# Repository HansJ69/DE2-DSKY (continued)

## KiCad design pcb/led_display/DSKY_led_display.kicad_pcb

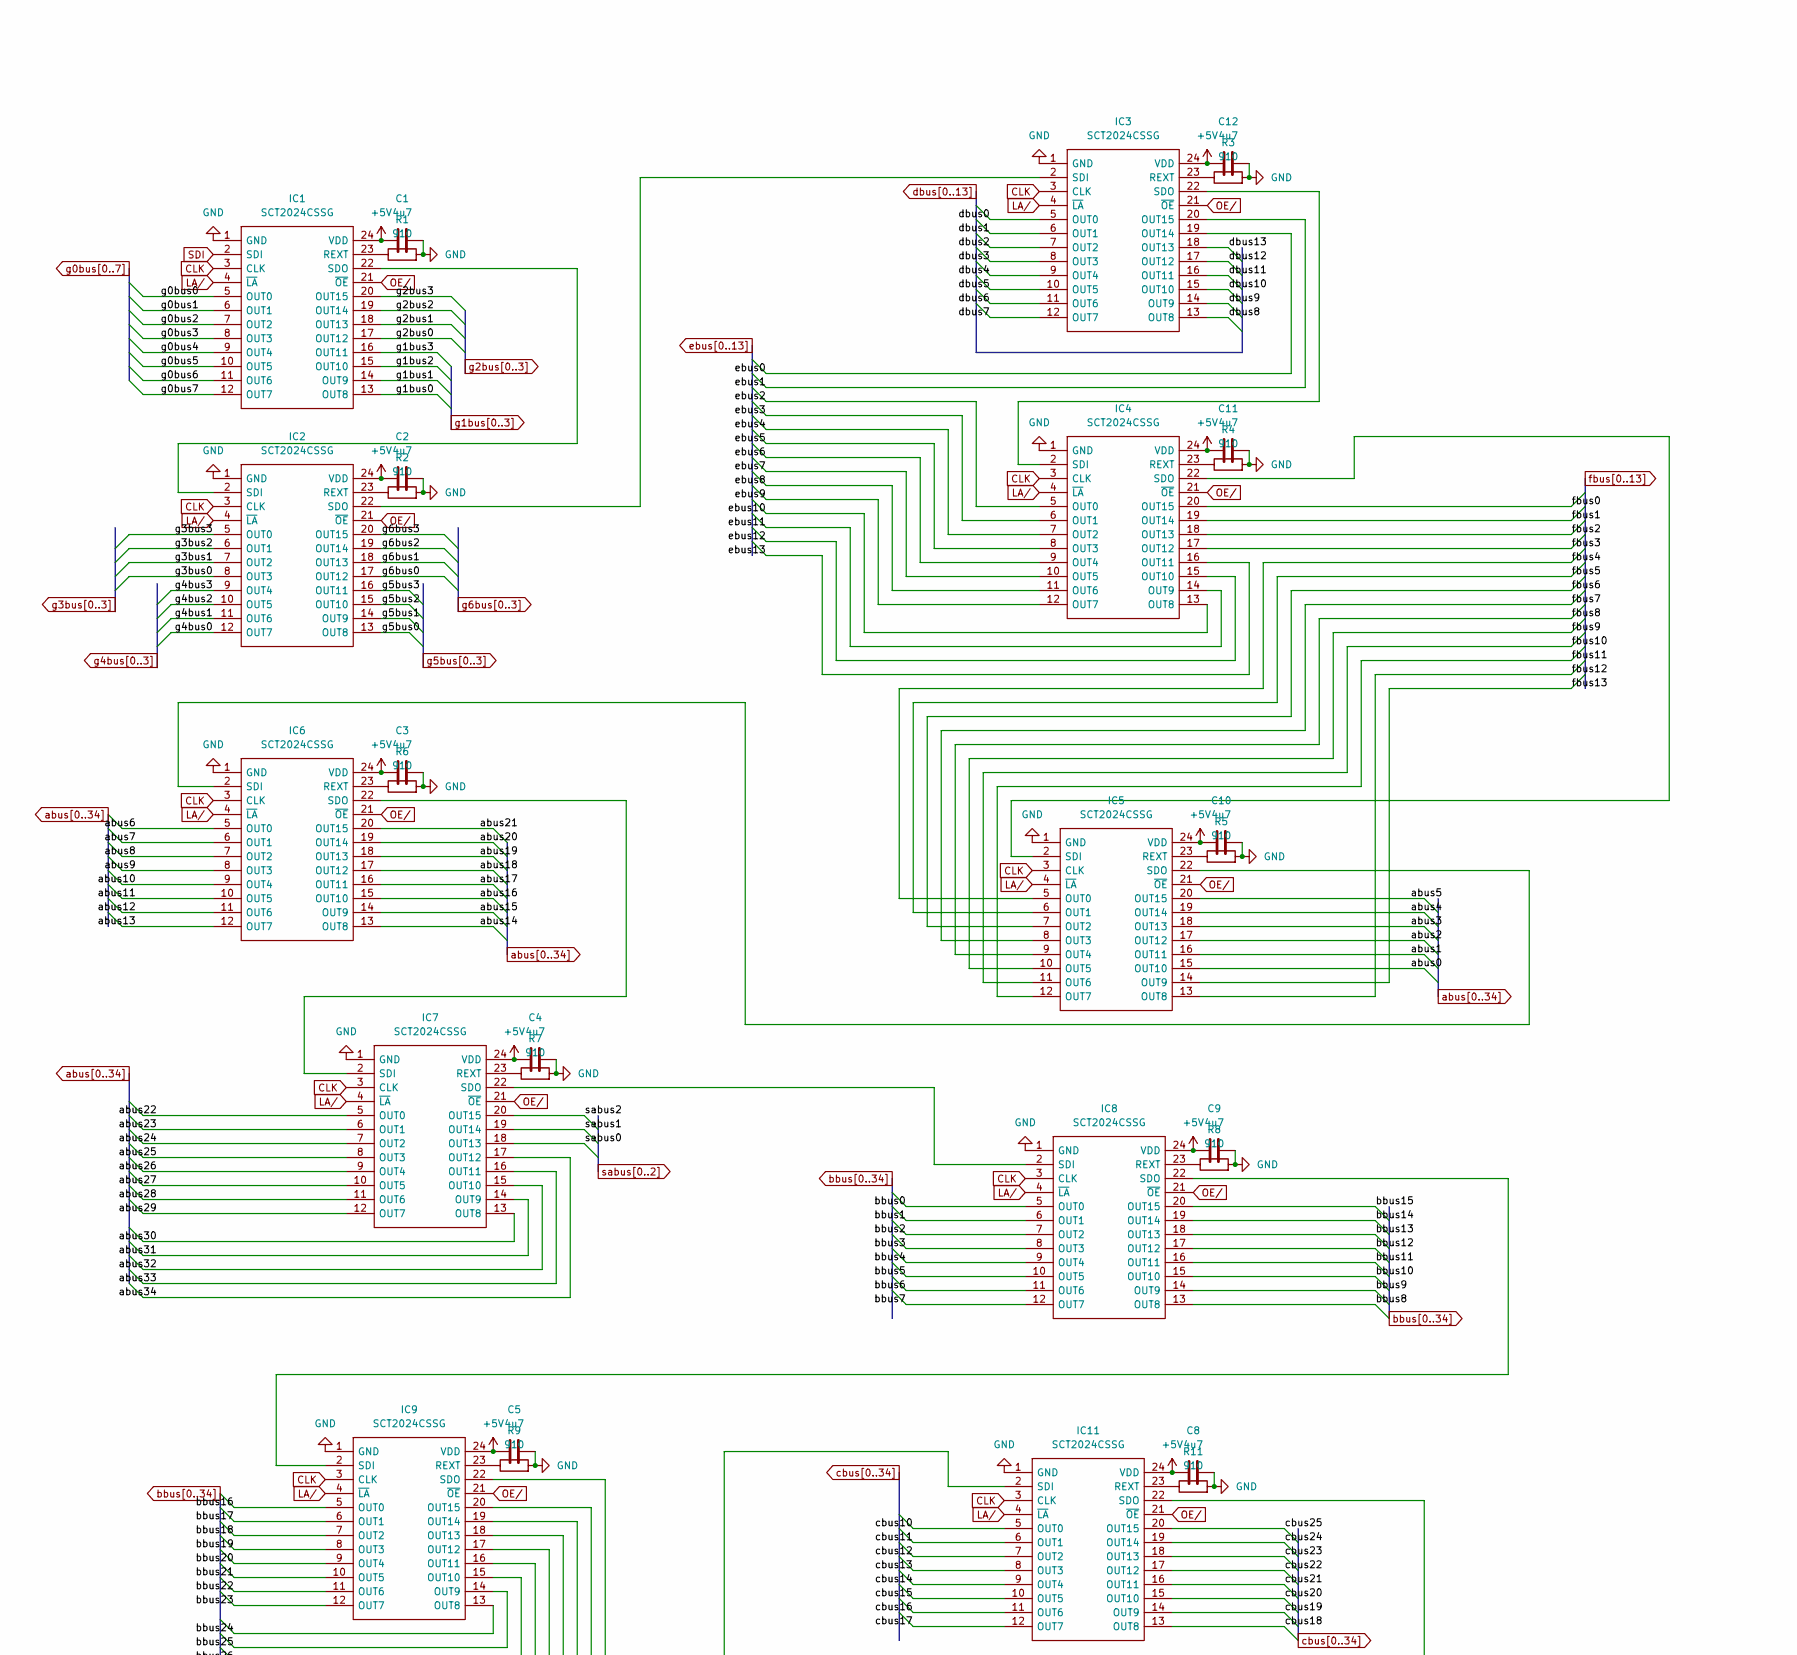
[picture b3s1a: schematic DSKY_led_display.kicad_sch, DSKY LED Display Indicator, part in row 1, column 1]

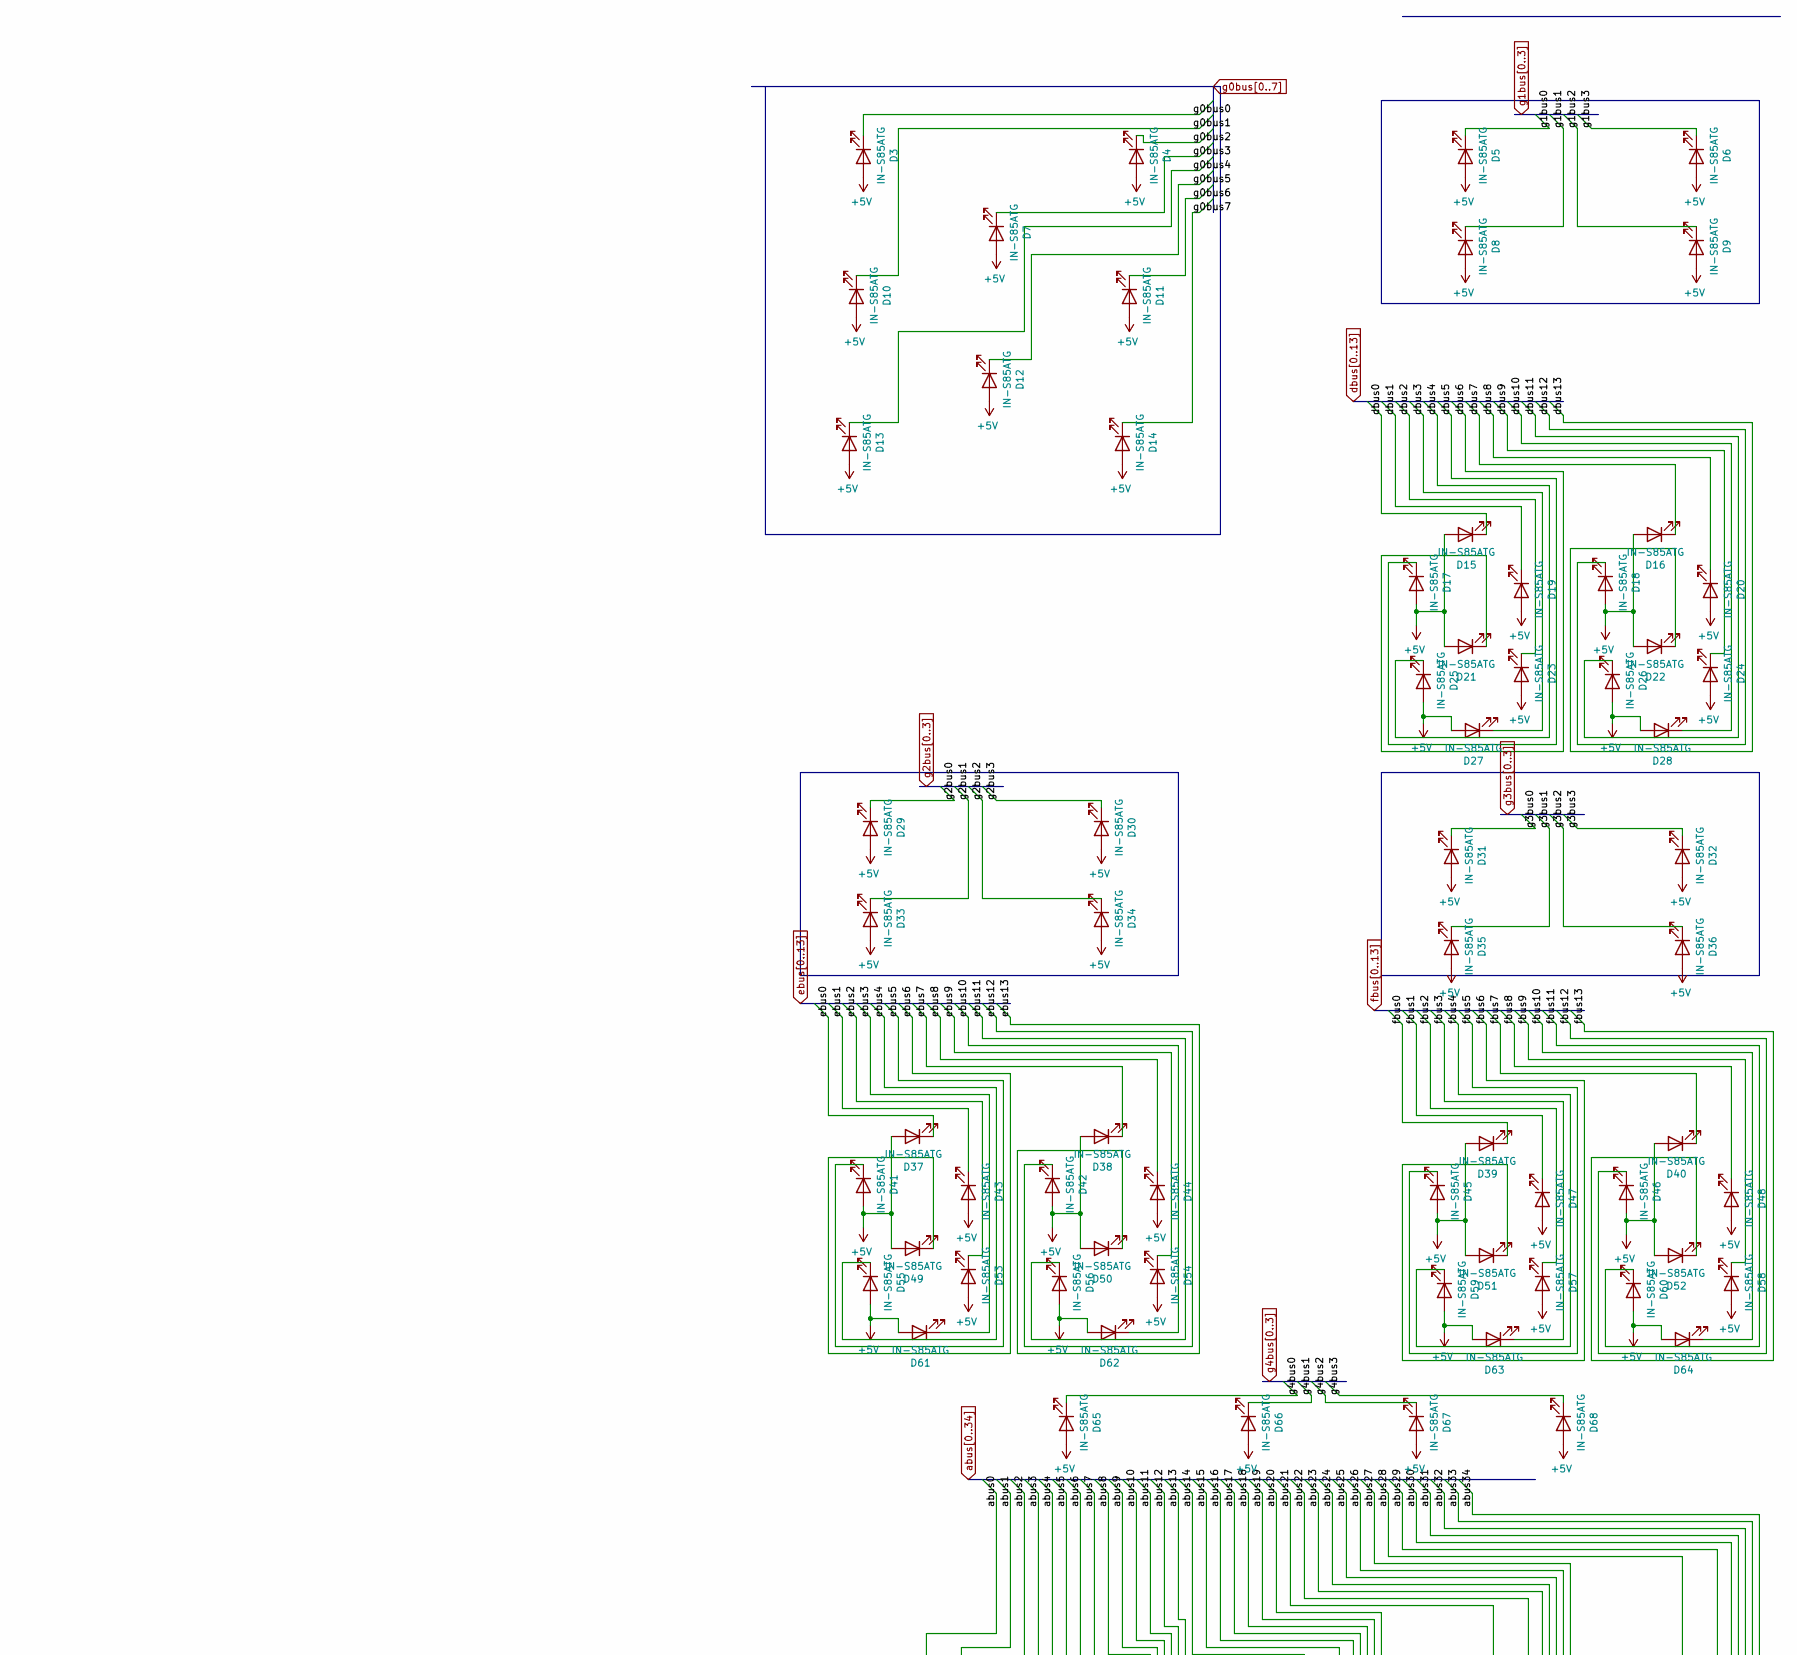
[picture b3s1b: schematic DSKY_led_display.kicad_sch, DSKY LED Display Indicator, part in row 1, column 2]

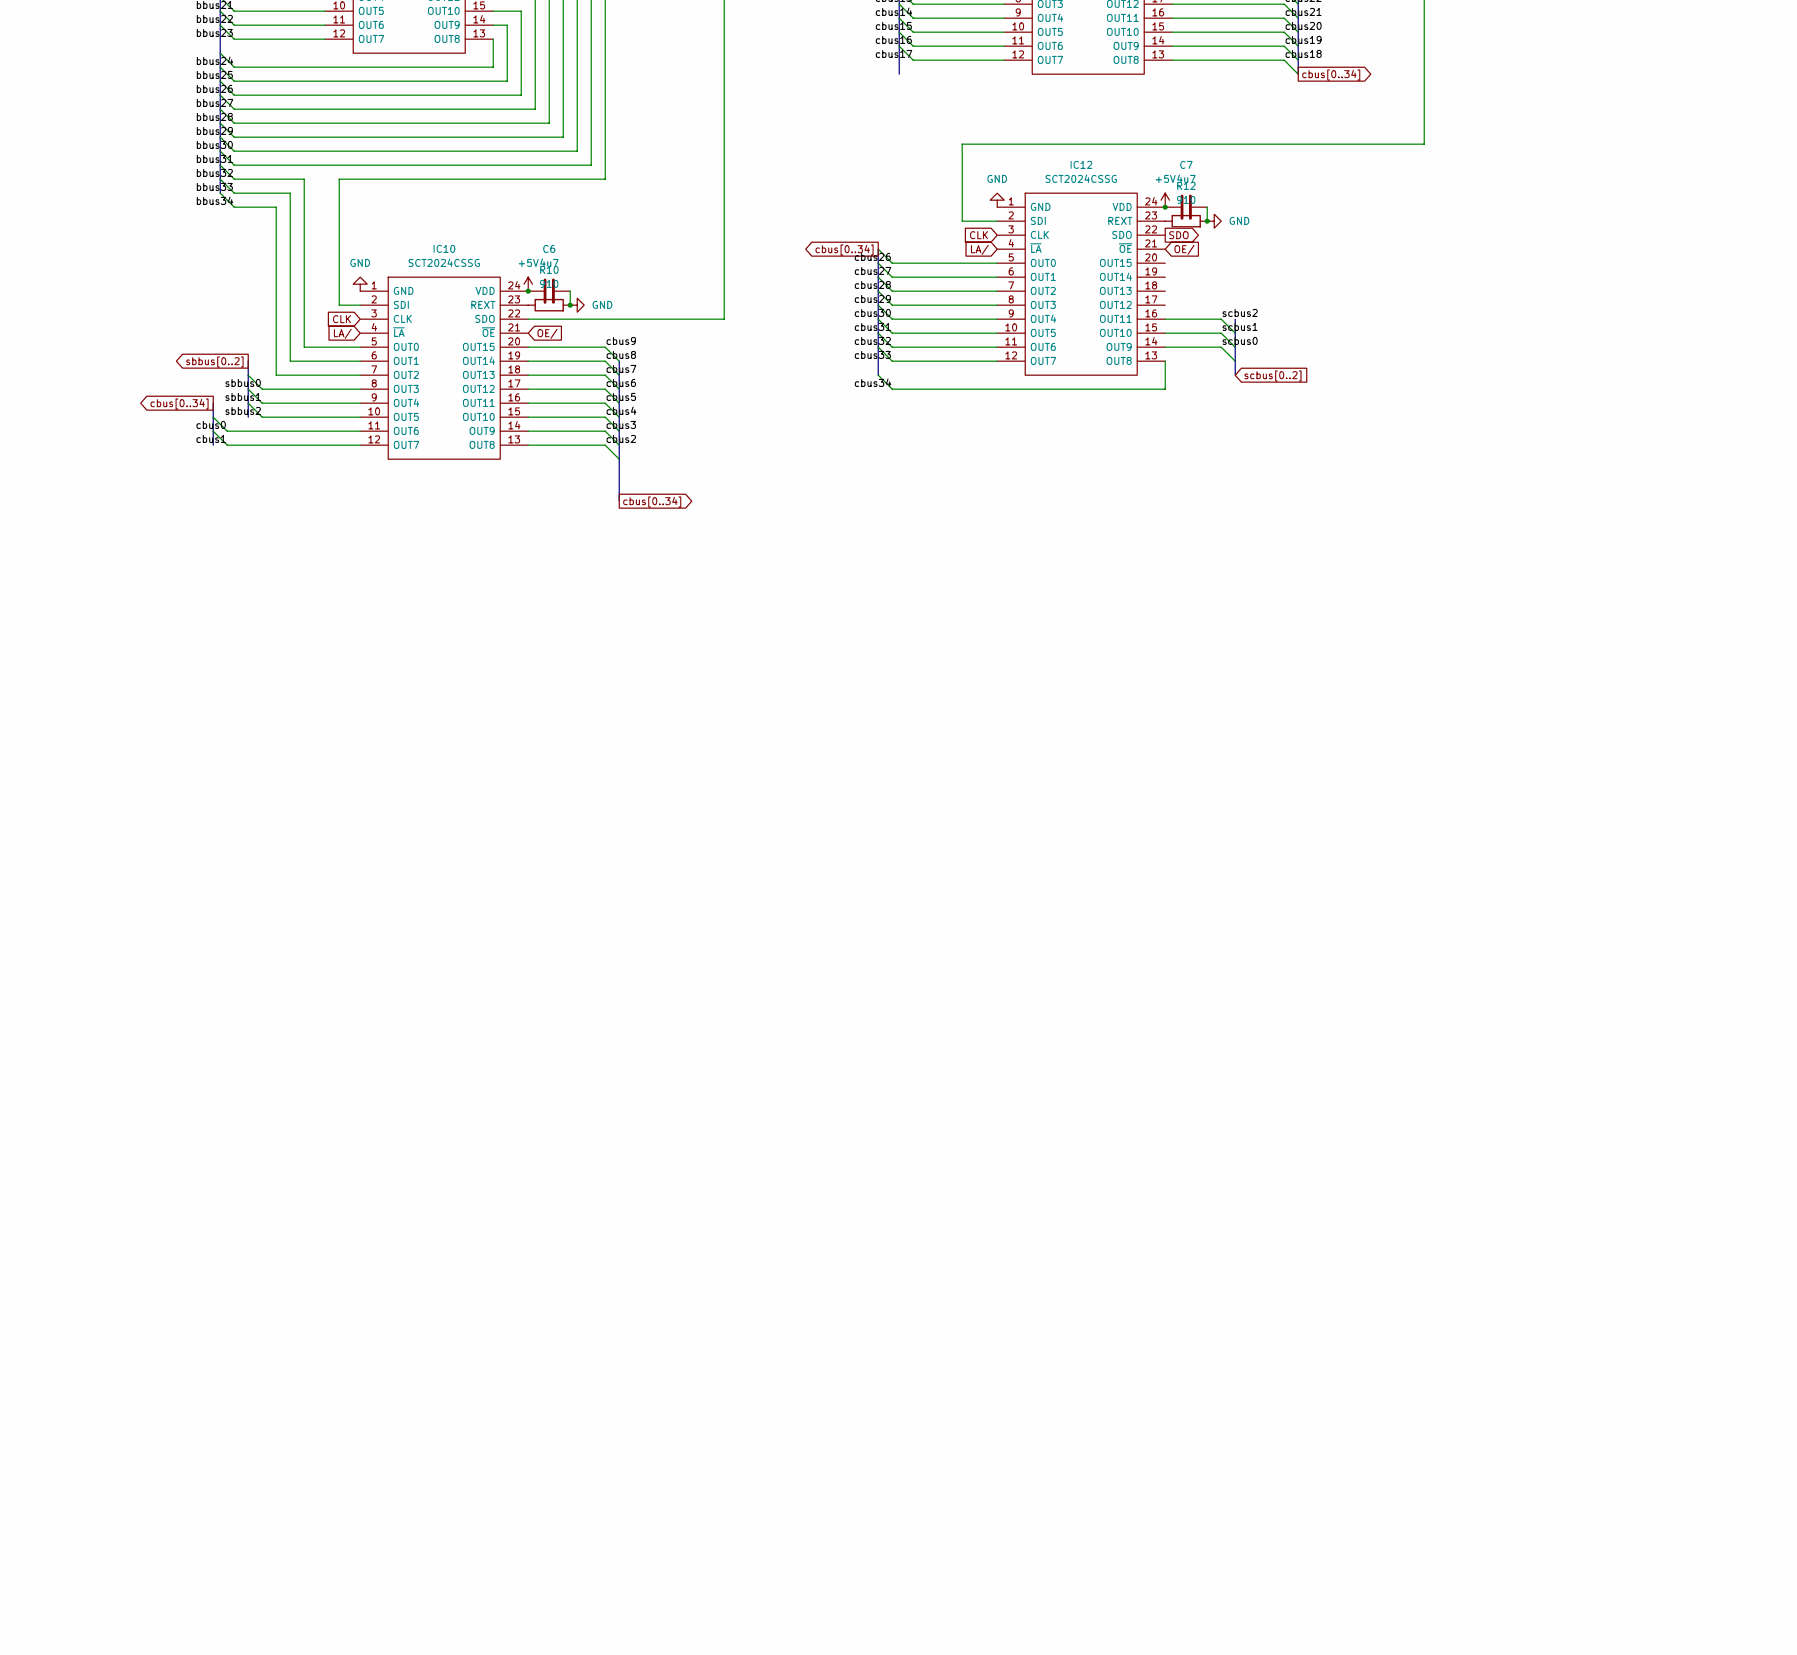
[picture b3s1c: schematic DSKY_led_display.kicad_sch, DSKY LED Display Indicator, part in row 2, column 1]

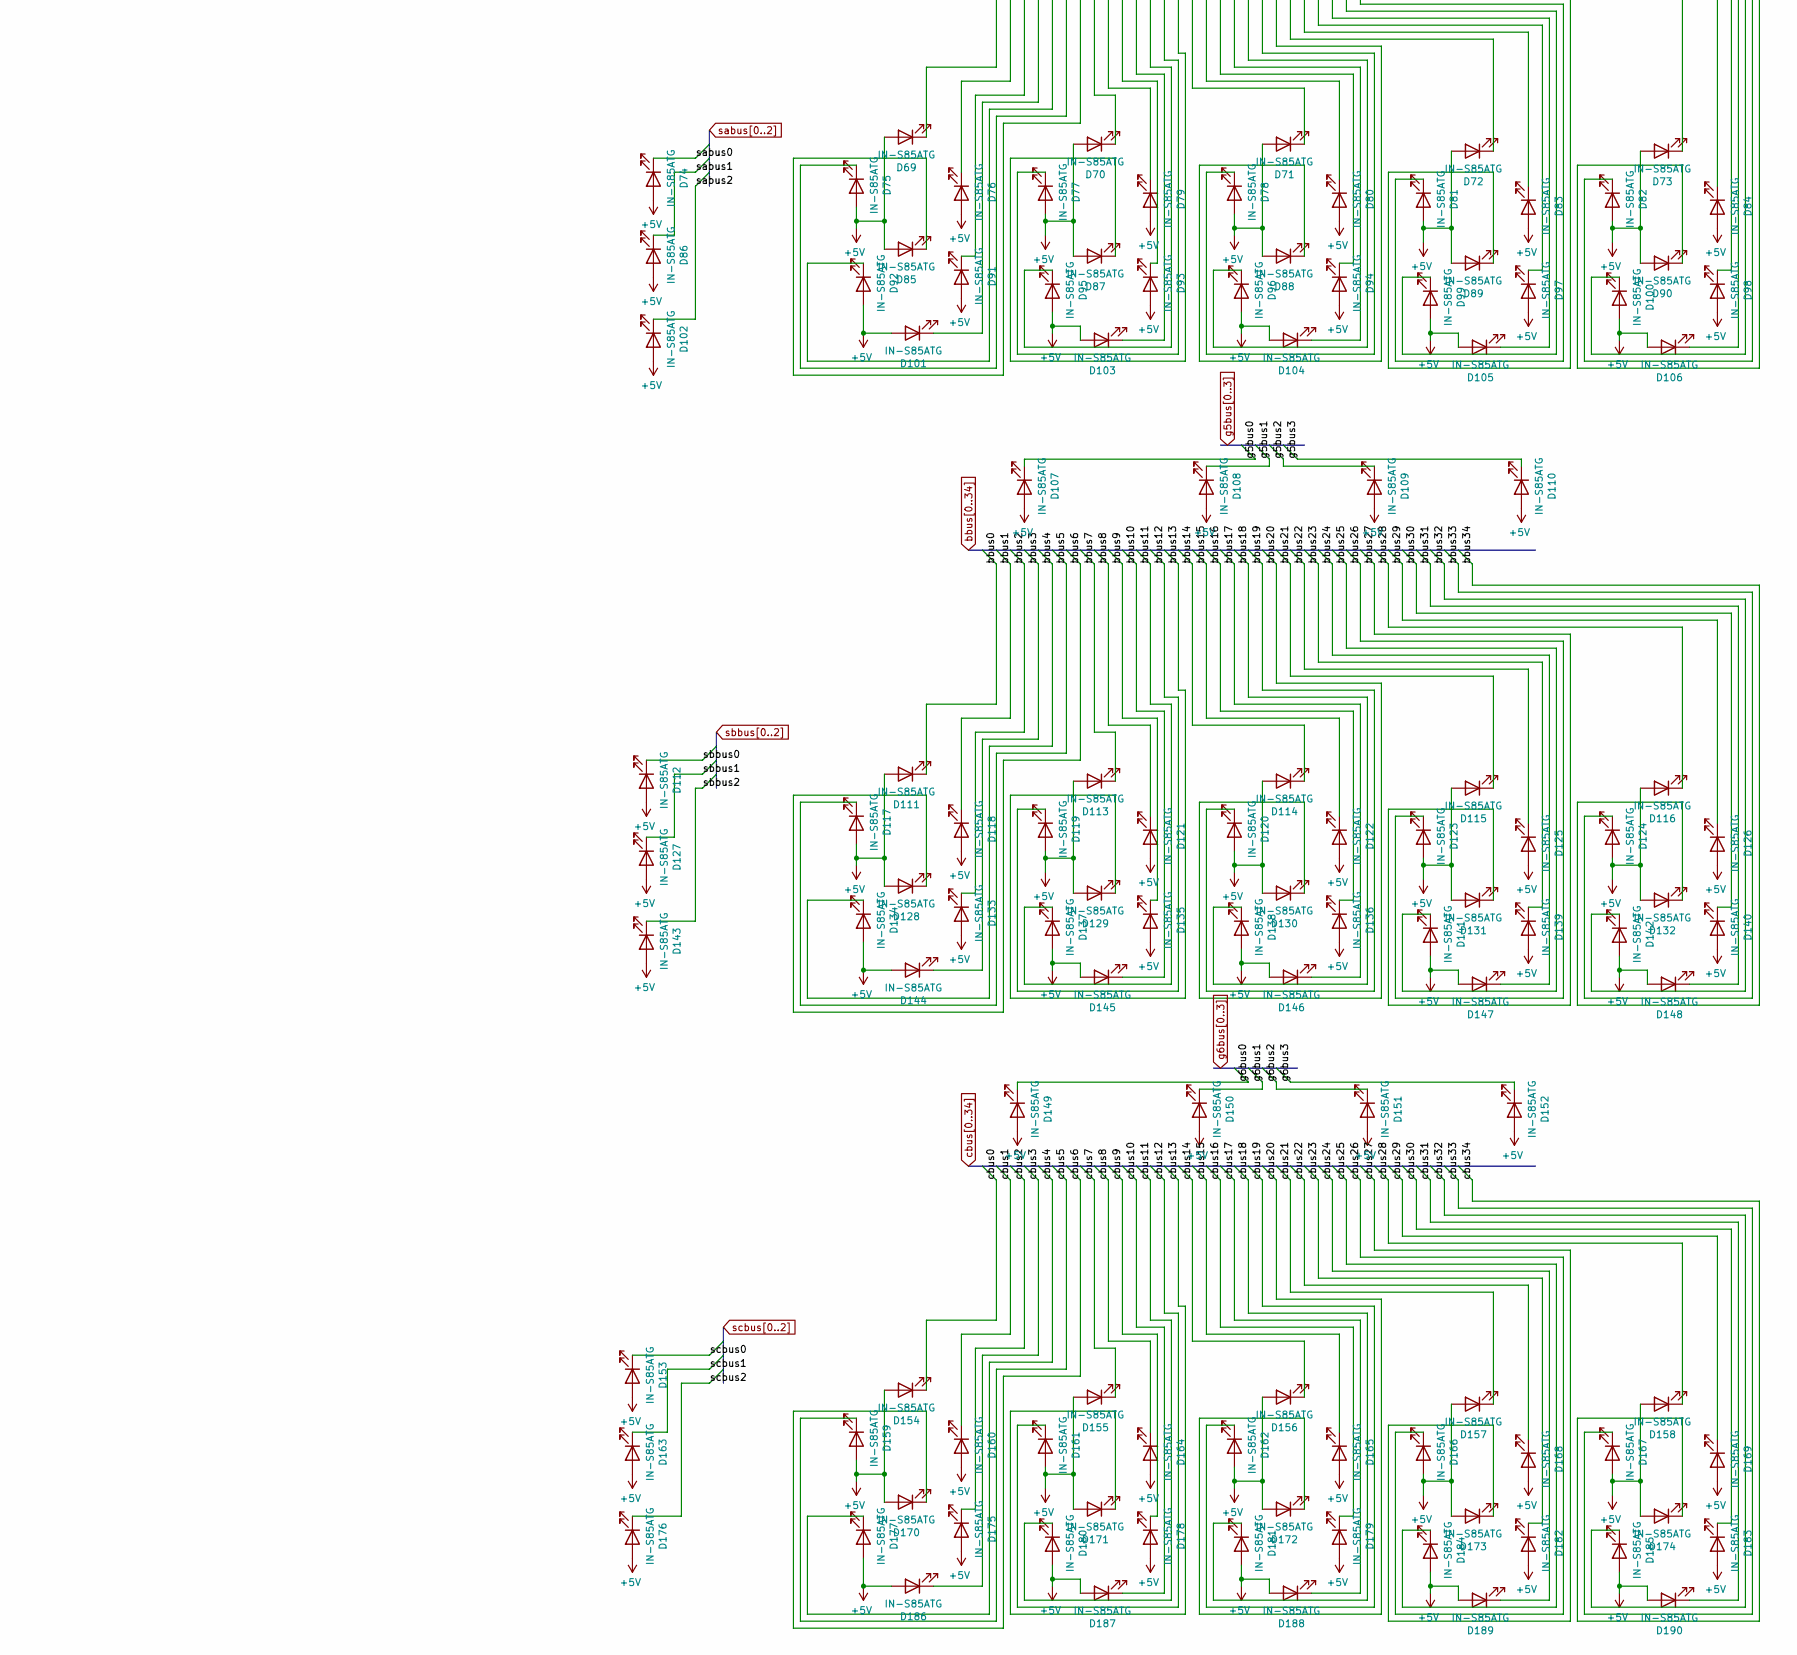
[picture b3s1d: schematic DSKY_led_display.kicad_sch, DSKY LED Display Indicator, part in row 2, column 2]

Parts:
C1, C2, C3, C4, C5, C6, C7, C8, C9, C10, C11, C12: 4u7; LED_0805_2012Metric_Pad1.15x1.40mm_HandSolder
D3, D4, D5, D6, D7, D8, D9, D10, D11, D12, D13, D14, D15, D16, D17, D18, D19, D20, D21, D22, D23, D24, D25, D26, D27, D28, D29, D30, D31, D32, D33, D34, D35, D36, D37, D38, D39, D40, D41, D42, D43, D44, D45, D46, D47, D48, D49, D50, D51, D52, D53, D54, D55, D56, D57, D58, D59, D60, D61, D62, D63, D64, D65, D66, D67, D68, D69, D70, D71, D72, D73, D74, D75, D76, D77, D78, D79, D80, D81, D82, D83, D84, D85, D86, D87, D88, D89, D90, D91, D92, D93, D94, D95, D96, D97, D98, D99, D100, D101, D102, D103, D104, D105, D106, D107, D108, D109, D110, D111, D112, D113, D114, D115, D116, D117, D118, D119, D120, D121, D122, D123, D124, D125, D126, D127, D128, D129, D130, D131, D132, D133, D134, D135, D136, D137, D138, D139, D140, D141, D142, D143, D144, D145, D146, D147, D148, D149, D150, D151, D152, D153, D154, D155, D156, D157, D158, D159, D160, D161, D162, D163, D164, D165, D166, D167, D168, D169, D170, D171, D172, D173, D174, D175, D176, D177, D178, D179, D180, D181, D182, D183, D184, D185, D186, D187, D188, D189, D190: IN-S85ATG; LED_0805_2012Metric; Digi-Key_PN 1830-1079-1-ND
IC1, IC2, IC3, IC4, IC5, IC6, IC7, IC8, IC9, IC10, IC11, IC12: SCT2024CSSG; SOP64P600X175-24N; Manufacturer_Part_Number SCT2024CSSG
R1, R2, R3, R4, R5, R6, R7, R8, R9, R10, R11, R12: 910; R_0805_2012Metric_Pad1.20x1.40mm_HandSolder

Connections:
CLK: IC1.3 (CLK), IC2.3 (CLK), IC3.3 (CLK), IC4.3 (CLK), IC5.3 (CLK), IC6.3 (CLK), IC7.3 (CLK), IC8.3 (CLK), IC9.3 (CLK), IC10.3 (CLK), IC11.3 (CLK), IC12.3 (CLK); also elsewhere on the board
GND: C1.2, C2.2, C3.2, C4.2, C5.2, C6.2, C7.2, C8.2, C9.2, C10.2, C11.2, C12.2, IC1.1 (GND), IC2.1 (GND), IC3.1 (GND), IC4.1 (GND), IC5.1 (GND), IC6.1 (GND), IC7.1 (GND), IC8.1 (GND), IC9.1 (GND), IC10.1 (GND), IC11.1 (GND), IC12.1 (GND), R1.2, R2.2, R3.2, R4.2, R5.2, R6.2, R7.2, R8.2, R9.2, R10.2, R11.2, R12.2; also elsewhere on the board
LA/: IC1.4 (~LA), IC2.4 (~LA), IC3.4 (~LA), IC4.4 (~LA), IC5.4 (~LA), IC6.4 (~LA), IC7.4 (~LA), IC8.4 (~LA), IC9.4 (~LA), IC10.4 (~LA), IC11.4 (~LA), IC12.4 (~LA); also elsewhere on the board
unnamed: IC1.23 (REXT), R1.1
unnamed: IC1.22 (SDO), IC2.2 (SDI)
unnamed: IC2.23 (REXT), R2.1
unnamed: IC2.22 (SDO), IC3.2 (SDI)
unnamed: IC3.23 (REXT), R3.1
unnamed: IC3.22 (SDO), IC4.2 (SDI)
unnamed: IC4.23 (REXT), R4.1
unnamed: IC4.22 (SDO), IC5.2 (SDI)
unnamed: IC5.23 (REXT), R5.1
unnamed: IC5.22 (SDO), IC6.2 (SDI)
unnamed: IC6.23 (REXT), R6.1
unnamed: IC6.22 (SDO), IC7.2 (SDI)
unnamed: IC7.23 (REXT), R7.1
unnamed: IC7.22 (SDO), IC8.2 (SDI)
unnamed: IC8.23 (REXT), R8.1
unnamed: IC8.22 (SDO), IC9.2 (SDI)
unnamed: IC9.23 (REXT), R9.1
unnamed: IC10.23 (REXT), R10.1
unnamed: IC9.22 (SDO), IC10.2 (SDI)
unnamed: IC10.22 (SDO), IC11.2 (SDI)
unnamed: IC11.23 (REXT), R11.1
unnamed: IC11.22 (SDO), IC12.2 (SDI)
unnamed: IC12.23 (REXT), R12.1
OE/: IC1.21 (~OE), IC2.21 (~OE), IC3.21 (~OE), IC4.21 (~OE), IC5.21 (~OE), IC6.21 (~OE), IC7.21 (~OE), IC8.21 (~OE), IC9.21 (~OE), IC10.21 (~OE), IC11.21 (~OE), IC12.21 (~OE); also elsewhere on the board
SDI: IC1.2 (SDI); also elsewhere on the board
SDO: IC12.22 (SDO); also elsewhere on the board
abus0: D69.1 (K), IC5.15 (OUT10)
abus1: D76.1 (K), IC5.16 (OUT11)
abus2: D91.1 (K), IC5.17 (OUT12)
abus3: D101.1 (K), IC5.18 (OUT13)
abus4: D92.1 (K), IC5.19 (OUT14)
abus5: D75.1 (K), IC5.20 (OUT15)
abus6: D85.1 (K), IC6.5 (OUT0)
abus7: D70.1 (K), IC6.6 (OUT1)
abus8: D79.1 (K), IC6.7 (OUT2)
abus9: D93.1 (K), IC6.8 (OUT3)
abus10: D103.1 (K), IC6.9 (OUT4)
abus11: D95.1 (K), IC6.10 (OUT5)
abus12: D77.1 (K), IC6.11 (OUT6)
abus13: D87.1 (K), IC6.12 (OUT7)
abus14: D71.1 (K), IC6.13 (OUT8)
abus15: D80.1 (K), IC6.14 (OUT9)
abus16: D94.1 (K), IC6.15 (OUT10)
abus17: D104.1 (K), IC6.16 (OUT11)
abus18: D96.1 (K), IC6.17 (OUT12)
abus19: D78.1 (K), IC6.18 (OUT13)
abus20: D88.1 (K), IC6.19 (OUT14)
abus21: D72.1 (K), IC6.20 (OUT15)
abus22: D83.1 (K), IC7.5 (OUT0)
abus23: D97.1 (K), IC7.6 (OUT1)
abus24: D105.1 (K), IC7.7 (OUT2)
abus25: D99.1 (K), IC7.8 (OUT3)
abus26: D81.1 (K), IC7.9 (OUT4)
abus27: D89.1 (K), IC7.10 (OUT5)
abus28: D73.1 (K), IC7.11 (OUT6)
abus29: D84.1 (K), IC7.12 (OUT7)
abus30: D98.1 (K), IC7.13 (OUT8)
abus31: D106.1 (K), IC7.14 (OUT9)
abus32: D100.1 (K), IC7.15 (OUT10)
abus33: D82.1 (K), IC7.16 (OUT11)
abus34: D90.1 (K), IC7.17 (OUT12)
bbus0: D111.1 (K), IC8.5 (OUT0)
bbus1: D118.1 (K), IC8.6 (OUT1)
bbus2: D133.1 (K), IC8.7 (OUT2)
bbus3: D144.1 (K), IC8.8 (OUT3)
bbus4: D134.1 (K), IC8.9 (OUT4)
bbus5: D117.1 (K), IC8.10 (OUT5)
bbus6: D128.1 (K), IC8.11 (OUT6)
bbus7: D113.1 (K), IC8.12 (OUT7)
bbus8: D121.1 (K), IC8.13 (OUT8)
bbus9: D135.1 (K), IC8.14 (OUT9)
bbus10: D145.1 (K), IC8.15 (OUT10)
bbus11: D137.1 (K), IC8.16 (OUT11)
bbus12: D119.1 (K), IC8.17 (OUT12)
bbus13: D129.1 (K), IC8.18 (OUT13)
bbus14: D114.1 (K), IC8.19 (OUT14)
bbus15: D122.1 (K), IC8.20 (OUT15)
bbus16: D136.1 (K), IC9.5 (OUT0)
bbus17: D146.1 (K), IC9.6 (OUT1)
bbus18: D138.1 (K), IC9.7 (OUT2)
bbus19: D120.1 (K), IC9.8 (OUT3)
bbus20: D130.1 (K), IC9.9 (OUT4)
bbus21: D115.1 (K), IC9.10 (OUT5)
bbus22: D125.1 (K), IC9.11 (OUT6)
bbus23: D139.1 (K), IC9.12 (OUT7)
bbus24: D147.1 (K), IC9.13 (OUT8)
bbus25: D141.1 (K), IC9.14 (OUT9)
bbus26: D123.1 (K), IC9.15 (OUT10)
bbus27: D131.1 (K), IC9.16 (OUT11)
bbus28: D116.1 (K), IC9.17 (OUT12)
bbus29: D126.1 (K), IC9.18 (OUT13)
bbus30: D140.1 (K), IC9.19 (OUT14)
bbus31: D148.1 (K), IC9.20 (OUT15)
bbus32: D142.1 (K), IC10.5 (OUT0)
bbus33: D124.1 (K), IC10.6 (OUT1)
bbus34: D132.1 (K), IC10.7 (OUT2)
cbus0: D154.1 (K), IC10.11 (OUT6)
cbus1: D160.1 (K), IC10.12 (OUT7)
cbus2: D175.1 (K), IC10.13 (OUT8)
cbus3: D186.1 (K), IC10.14 (OUT9)
cbus4: D177.1 (K), IC10.15 (OUT10)
cbus5: D159.1 (K), IC10.16 (OUT11)
cbus6: D170.1 (K), IC10.17 (OUT12)
cbus7: D155.1 (K), IC10.18 (OUT13)
cbus8: D164.1 (K), IC10.19 (OUT14)
cbus9: D178.1 (K), IC10.20 (OUT15)
cbus10: D187.1 (K), IC11.5 (OUT0)
cbus11: D180.1 (K), IC11.6 (OUT1)
cbus12: D161.1 (K), IC11.7 (OUT2)
cbus13: D171.1 (K), IC11.8 (OUT3)
cbus14: D156.1 (K), IC11.9 (OUT4)
cbus15: D165.1 (K), IC11.10 (OUT5)
cbus16: D179.1 (K), IC11.11 (OUT6)
cbus17: D188.1 (K), IC11.12 (OUT7)
cbus18: D181.1 (K), IC11.13 (OUT8)
cbus19: D162.1 (K), IC11.14 (OUT9)
cbus20: D172.1 (K), IC11.15 (OUT10)
cbus21: D157.1 (K), IC11.16 (OUT11)
cbus22: D168.1 (K), IC11.17 (OUT12)
cbus23: D182.1 (K), IC11.18 (OUT13)
cbus24: D189.1 (K), IC11.19 (OUT14)
cbus25: D184.1 (K), IC11.20 (OUT15)
cbus26: D166.1 (K), IC12.5 (OUT0)
cbus27: D173.1 (K), IC12.6 (OUT1)
cbus28: D158.1 (K), IC12.7 (OUT2)
cbus29: D169.1 (K), IC12.8 (OUT3)
cbus30: D183.1 (K), IC12.9 (OUT4)
cbus31: D190.1 (K), IC12.10 (OUT5)
cbus32: D185.1 (K), IC12.11 (OUT6)
cbus33: D167.1 (K), IC12.12 (OUT7)
cbus34: D174.1 (K), IC12.13 (OUT8)
dbus0: D15.1 (K), IC3.5 (OUT0)
dbus1: D19.1 (K), IC3.6 (OUT1)
dbus2: D23.1 (K), IC3.7 (OUT2)
dbus3: D27.1 (K), IC3.8 (OUT3)
dbus4: D25.1 (K), IC3.9 (OUT4)
dbus5: D17.1 (K), IC3.10 (OUT5)
dbus6: D21.1 (K), IC3.11 (OUT6)
dbus7: D16.1 (K), IC3.12 (OUT7)
dbus8: D20.1 (K), IC3.13 (OUT8)
dbus9: D24.1 (K), IC3.14 (OUT9)
dbus10: D28.1 (K), IC3.15 (OUT10)
dbus11: D26.1 (K), IC3.16 (OUT11)
dbus12: D18.1 (K), IC3.17 (OUT12)
dbus13: D22.1 (K), IC3.18 (OUT13)
ebus0: D37.1 (K), IC3.19 (OUT14)
ebus1: D43.1 (K), IC3.20 (OUT15)
ebus2: D53.1 (K), IC4.5 (OUT0)
ebus3: D61.1 (K), IC4.6 (OUT1)
ebus4: D55.1 (K), IC4.7 (OUT2)
ebus5: D41.1 (K), IC4.8 (OUT3)
ebus6: D49.1 (K), IC4.9 (OUT4)
ebus7: D38.1 (K), IC4.10 (OUT5)
ebus8: D44.1 (K), IC4.11 (OUT6)
ebus9: D54.1 (K), IC4.12 (OUT7)
ebus10: D62.1 (K), IC4.13 (OUT8)
ebus11: D56.1 (K), IC4.14 (OUT9)
ebus12: D42.1 (K), IC4.15 (OUT10)
ebus13: D50.1 (K), IC4.16 (OUT11)
fbus0: D39.1 (K), IC4.20 (OUT15)
fbus1: D47.1 (K), IC4.19 (OUT14)
fbus2: D57.1 (K), IC4.18 (OUT13)
fbus3: D63.1 (K), IC4.17 (OUT12)
fbus4: D59.1 (K), IC5.5 (OUT0)
fbus5: D45.1 (K), IC5.6 (OUT1)
fbus6: D51.1 (K), IC5.7 (OUT2)
fbus7: D40.1 (K), IC5.8 (OUT3)
fbus8: D48.1 (K), IC5.9 (OUT4)
fbus9: D58.1 (K), IC5.10 (OUT5)
fbus10: D64.1 (K), IC5.11 (OUT6)
fbus11: D60.1 (K), IC5.12 (OUT7)
fbus12: D46.1 (K), IC5.13 (OUT8)
fbus13: D52.1 (K), IC5.14 (OUT9)
g0bus0: D3.1 (K), IC1.5 (OUT0)
g0bus1: D10.1 (K), IC1.6 (OUT1)
g0bus2: D4.1 (K), IC1.7 (OUT2)
g0bus3: D7.1 (K), IC1.8 (OUT3)
g0bus4: D13.1 (K), IC1.9 (OUT4)
g0bus5: D12.1 (K), IC1.10 (OUT5)
g0bus6: D11.1 (K), IC1.11 (OUT6)
g0bus7: D14.1 (K), IC1.12 (OUT7)
g1bus0: D5.1 (K), IC1.13 (OUT8)
g1bus1: D8.1 (K), IC1.14 (OUT9)
g1bus2: D9.1 (K), IC1.15 (OUT10)
g1bus3: D6.1 (K), IC1.16 (OUT11)
g2bus0: D29.1 (K), IC1.17 (OUT12)
g2bus1: D33.1 (K), IC1.18 (OUT13)
g2bus2: D34.1 (K), IC1.19 (OUT14)
g2bus3: D30.1 (K), IC1.20 (OUT15)
g3bus0: D31.1 (K), IC2.8 (OUT3)
g3bus1: D35.1 (K), IC2.7 (OUT2)
g3bus2: D36.1 (K), IC2.6 (OUT1)
g3bus3: D32.1 (K), IC2.5 (OUT0)
g4bus0: D65.1 (K), IC2.12 (OUT7)
g4bus1: D66.1 (K), IC2.11 (OUT6)
g4bus2: D67.1 (K), IC2.10 (OUT5)
g4bus3: D68.1 (K), IC2.9 (OUT4)
g5bus0: D107.1 (K), IC2.13 (OUT8)
g5bus1: D108.1 (K), IC2.14 (OUT9)
g5bus2: D109.1 (K), IC2.15 (OUT10)
g5bus3: D110.1 (K), IC2.16 (OUT11)
g6bus0: D149.1 (K), IC2.17 (OUT12)
g6bus1: D150.1 (K), IC2.18 (OUT13)
g6bus2: D151.1 (K), IC2.19 (OUT14)
g6bus3: D152.1 (K), IC2.20 (OUT15)
sabus0: D74.1 (K), IC7.18 (OUT13)
sabus1: D86.1 (K), IC7.19 (OUT14)
sabus2: D102.1 (K), IC7.20 (OUT15)
sbbus0: D112.1 (K), IC10.8 (OUT3)
sbbus1: D127.1 (K), IC10.9 (OUT4)
sbbus2: D143.1 (K), IC10.10 (OUT5)
scbus0: D153.1 (K), IC12.14 (OUT9)
scbus1: D163.1 (K), IC12.15 (OUT10)
scbus2: D176.1 (K), IC12.16 (OUT11)

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
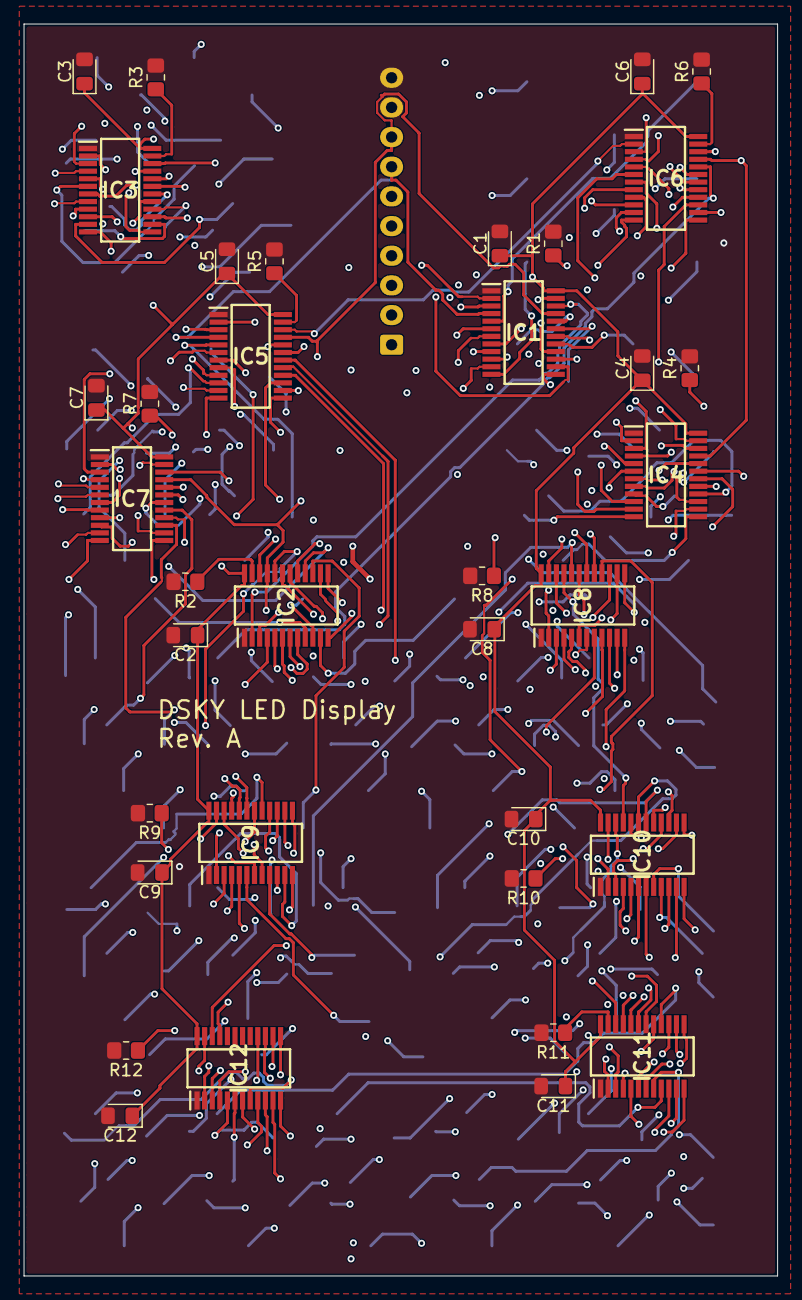
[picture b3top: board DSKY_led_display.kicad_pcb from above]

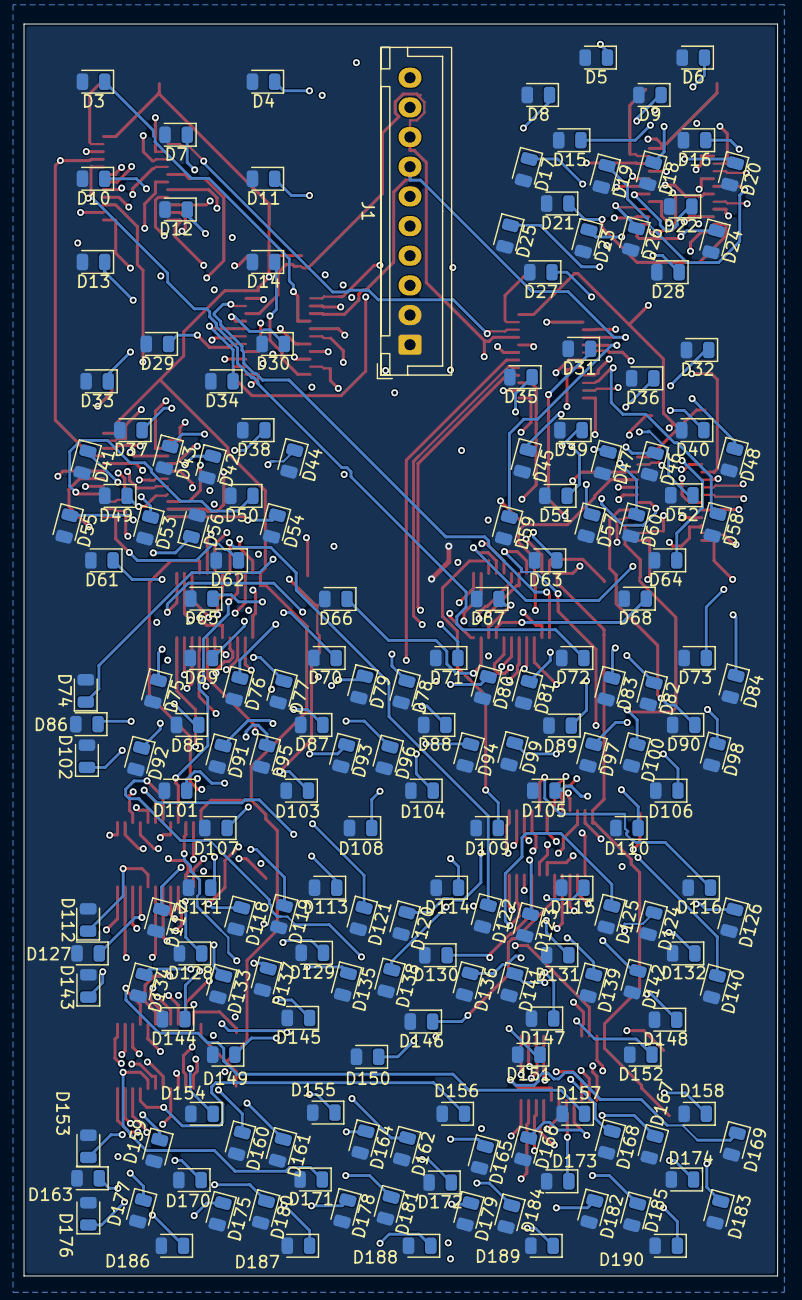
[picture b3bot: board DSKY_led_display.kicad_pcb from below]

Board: 4 copper layers, 63.5 x 105.5 mm, 225 parts (189 on the bottom side), 219 nets.

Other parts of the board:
J1: Conn_01x10; JST_XH_B10B-XH-A_1x10_P2.50mm_Vertical

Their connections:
CLK: J1.6; also elsewhere on the board
GND: J1.9, J1.10; also elsewhere on the board
LA/: J1.7; also elsewhere on the board
OE/: J1.8; also elsewhere on the board
SDI: J1.5; also elsewhere on the board
SDO: J1.4; also elsewhere on the board
